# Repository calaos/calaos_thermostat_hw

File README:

This project is intended to proide hardware materials and calaos configuration to build a Thermostat for Raspberrypi.

The hardware part is a basic Raspberry B+ HAT and contains
- 1 relay
- Support for 1wire DS18B20
- Teleinfo serial line

This project is perfect to control a Gaz heating system. The relay can activate/deactivate the heating system. The 1Wire bus can be used to connect a Temperature sensor. The teleinfo serial line, is specific to Enedis (ex ERDF) power meters.

You will also find the correspoding Calaos configuration, containing the declaration of all IO and the rules to get your thermostat working.

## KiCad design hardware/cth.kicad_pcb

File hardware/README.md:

# Calaos Thermostat Hardware

This directory contains all design files for Calaos Thermostat Hat for Rasperry PI.
Those files must be used with [Kicad](http://kicad-pcb.org/), the open source electronic CAO software

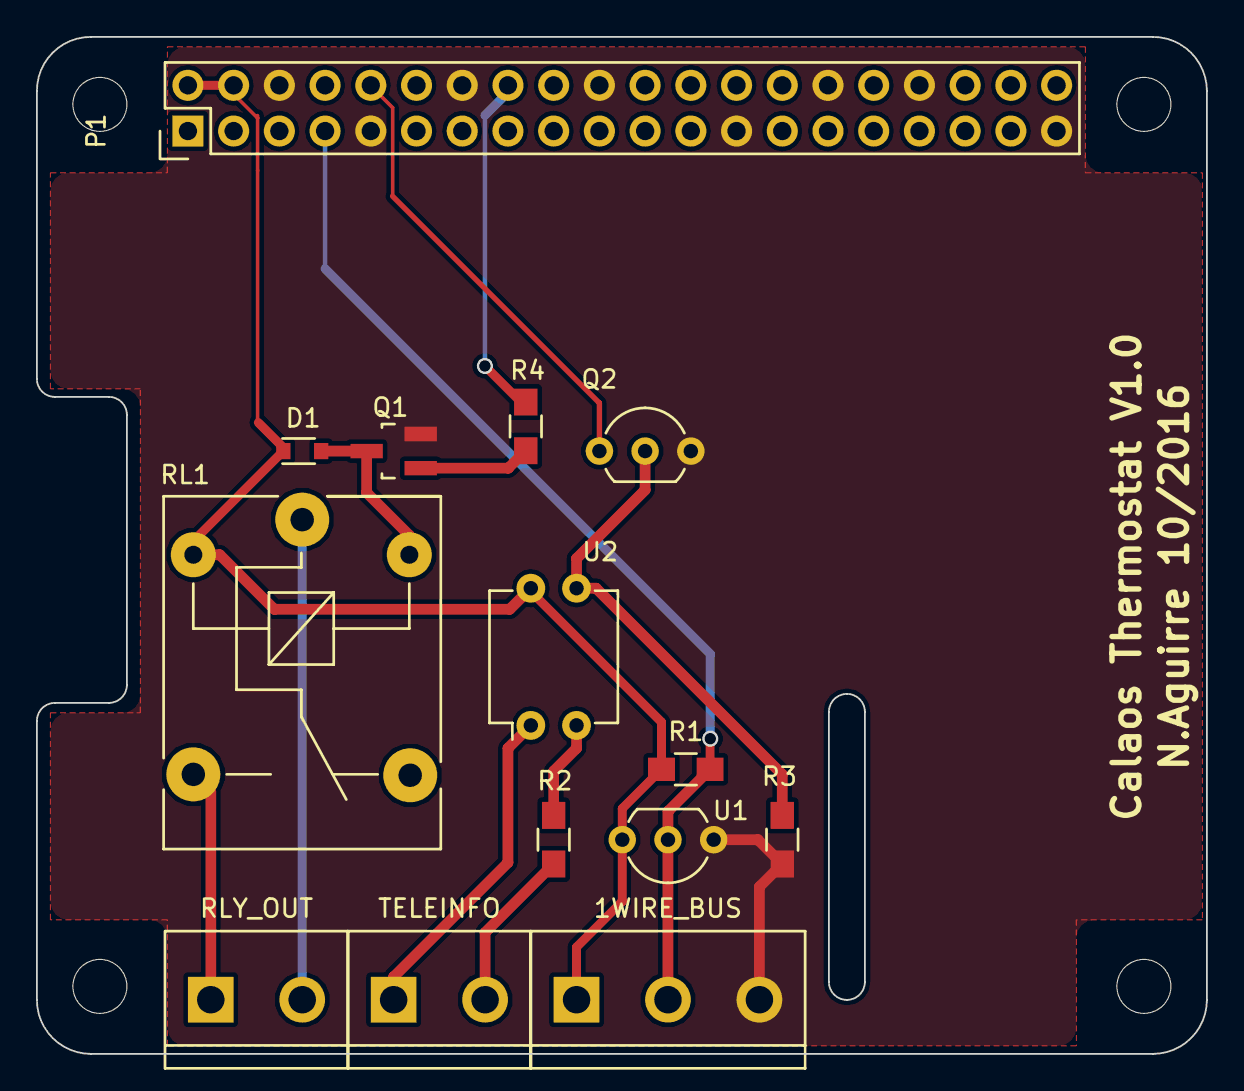
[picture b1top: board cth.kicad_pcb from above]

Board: 2 copper layers, 65.0 x 56.5 mm, 14 parts (0 on the bottom side), 13 nets.

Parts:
D1: D; D_0805
P1: Raspberry_Pi_+_Conn; Pin_Header_Straight_2x20
P2: TELEINFO; bornier2
P4: 1WIRE_BUS; bornier3
Q1: BC818-40; SOT-23_Handsoldering
Q2: BS170; TO-92_Inline_Wide
R1: 4k7; R_0805_HandSoldering
R2, R3, R4: R; R_0805_HandSoldering
RL1: SRD-XXVDC; Relay_SANYOU_SRD_Series_Form_C
RLY_OUT: RELAY_OUTPUT_1; bornier2
U1: DS18B20; TO-92_Inline_Wide
U2: LTV-814; DIP-4_W7.62mm

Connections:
+5V: D1.1, P1.2, P1.4, P4.1, R1.1, RL1.2, U1.3, U2.4
/1WD: P1.7, P4.2, R1.2, U1.2
/RELAY_CMD: P1.16, R4.1
/RXD: P1.10, Q2.1
GND: P1.6, P1.9, P1.14, P1.20, P1.25, P1.30, P1.34, P1.39, P4.3, Q1.2, Q2.3, R3.2, U1.1
unnamed: D1.2, Q1.3, RL1.5
unnamed: P2.1, U2.1
unnamed: P2.2, R2.2
unnamed: RL1.3, RLY_OUT.1
unnamed: RL1.1, RLY_OUT.2
unnamed: Q1.1, R4.2
unnamed: Q2.2, R3.1, U2.3
unnamed: R2.1, U2.2

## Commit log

2016-11-16 Update pdf schematics
2017-11-12 Add .gitignore
2017-11-12 Update README to markdown
2017-11-18 Add doc for software configuration example
2017-11-18 Add doc for hardware directory

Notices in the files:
hardware/cth.kicad_pcb:
License: CERN OHL V1.2
